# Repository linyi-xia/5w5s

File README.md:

# 5 Watt 5 Seconds (5W5S)
The project was funded by California Energy Commission back in 2011. 
- Phase 1
- Phase 2

# Project Team under project PI Prof. G.P. Li:
- Dr. Jieping Guo: Project lead
- Zac Davis: Phase 1 hardware
- Chris Hurst: Phase 1 hardware
- Linyi Xia: Phase 2 hardware lead engineer, partially firmware and software visualization 
- Liqiang Wang: Phase 2 visualization
- Other members

# Other useful links:
- [ThingSpeak] (https://thingspeak.com/channels/19678)

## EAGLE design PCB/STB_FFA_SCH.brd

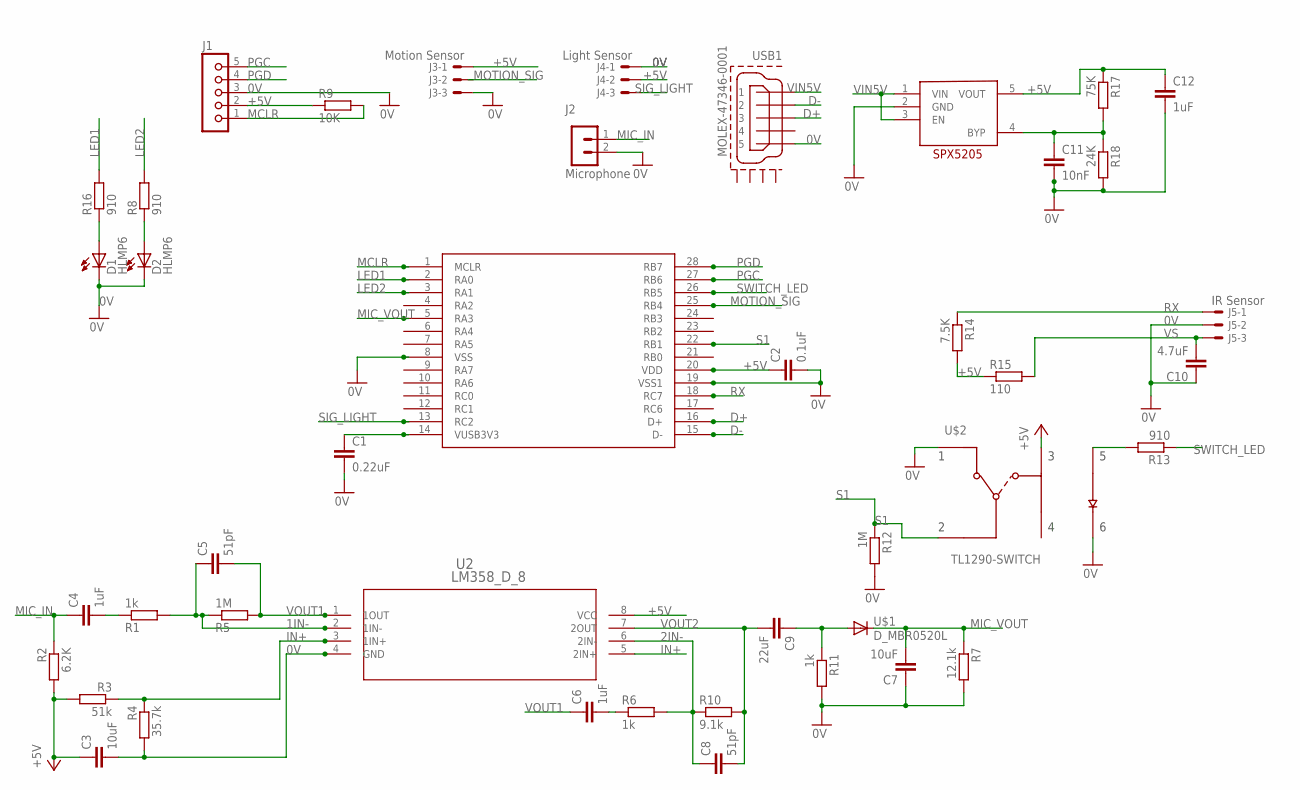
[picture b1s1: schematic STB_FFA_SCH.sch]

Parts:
C1: 0.22uF; C0805
C2: 0.1uF; C0805
C3, C7: 10uF; C0805
C4, C6, C12: 1uF; C0805
C5, C8: 51pF; C0805
C9: 22uF; C0805
C10: 4.7uF; C0805
C11: 10nF; C0805
D1, D2: HLMP6
J1: JU05
J2: Microphone; MA02-1
J3: Motion Sensor; 22-23-2031
J4: Light Sensor; 22-23-2031
J5: IR Sensor; 22-23-2031
R1, R6, R11: 1k; R0805
R2: 6.2K; R0805
R3: 51k; R0805
R4: 35.7k; R0805
R5, R12: 1M; R0805
R7: 12.1k; R0805
R8, R13, R16: 910; R0805
R9: 10K; R0805
R10: 9.1k; R0805
R14: 7.5K; R0805
R15: 110; R0805
R17: 75K; R0805
R18: 24K; R0805
U2: LM358_D_8; D8
U$1: D_MBR0520L
U$2: TL1290-SWITCH
U$3: SPX5205; SOT23-5
U$4: PIC18F25K500; SSOP28
USB1: MOLEX-47346-0001; MOLEX-47364-0001

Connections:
0V: C1.2, C2.2, C3.2, C7.1, C10.1, C11.2, C12.2, D1.K, D2.K, J1.3, J2.2, J3.3, J4.1, J5.2, R4.2, R7.2, R11.2, R12.2, R18.2, U2.4 (GND), U$2.1, U$2.6, U$3.2 (GND), U$4.8 (VSS), U$4.19 (VSS1), USB1.5
1IN-: C5.1, R1.2, R5.1, U2.2 (1IN-)
2IN-: C8.1, R6.2, R10.1, U2.6 (2IN-)
+5V: C2.1, C3.1, C12.1, J1.2, J3.1, J4.2, R2.2, R3.2, R9.1, R14.2, R15.1, R17.1, U2.8 (VCC), U$2.3, U$3.5 (VOUT), U$4.20 (VDD)
D+: U$4.16 (D+), USB1.3
D-: U$4.15 (D-), USB1.2
IN+: R3.1, R4.1, U2.3 (1IN+), U2.5 (2IN+)
LED1: R16.2, U$4.2 (RA0)
LED2: R8.2, U$4.3 (RA1)
MCLR: J1.1, R9.2, U$4.1 (MCLR)
MIC_IN: C4.1, J2.1, R2.1
MIC_VOUT: C7.2, R7.1, U$1.C, U$4.5 (RA3)
MOTION_SIG: U$4.25 (RB4)
unnamed: C1.1, U$4.14 (VUSB3V3)
unnamed: D2.A, R8.1
unnamed: C9.1, R11.1, U$1.A
unnamed: C6.2, R6.1
unnamed: R13.2, U$2.5
unnamed: D1.A, R16.1
unnamed: C4.2, R1.1
unnamed: C11.1, R17.2, R18.1, U$3.4 (BYP)
PGC: J1.5, U$4.27 (RB6)
PGD: J1.4, U$4.28 (RB7)
RX: J5.1, R14.1, U$4.18 (RC7)
S1: R12.1, U$2.2, U$4.22 (RB1)
SIG_LIGHT: J4.3, U$4.13 (RC2)
SWITCH_LED: R13.1, U$4.26 (RB5)
VIN5V: U$3.1 (VIN), U$3.3 (EN), USB1.1
VOUT1: C5.2, C6.1, R5.2, U2.1 (1OUT)
VOUT2: C8.2, C9.2, R10.2, U2.7 (2OUT)
VS: C10.2, J5.3, R15.2

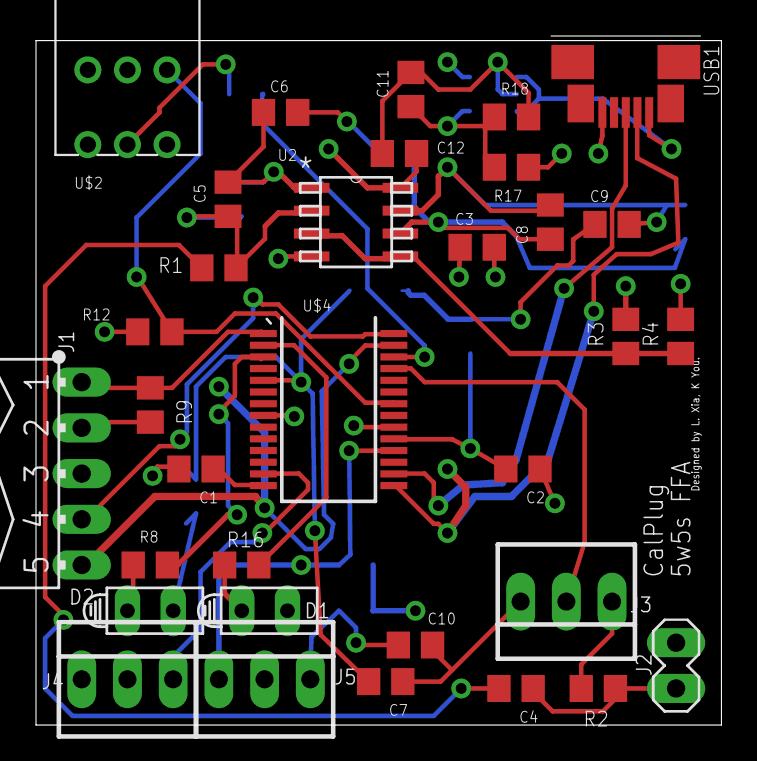
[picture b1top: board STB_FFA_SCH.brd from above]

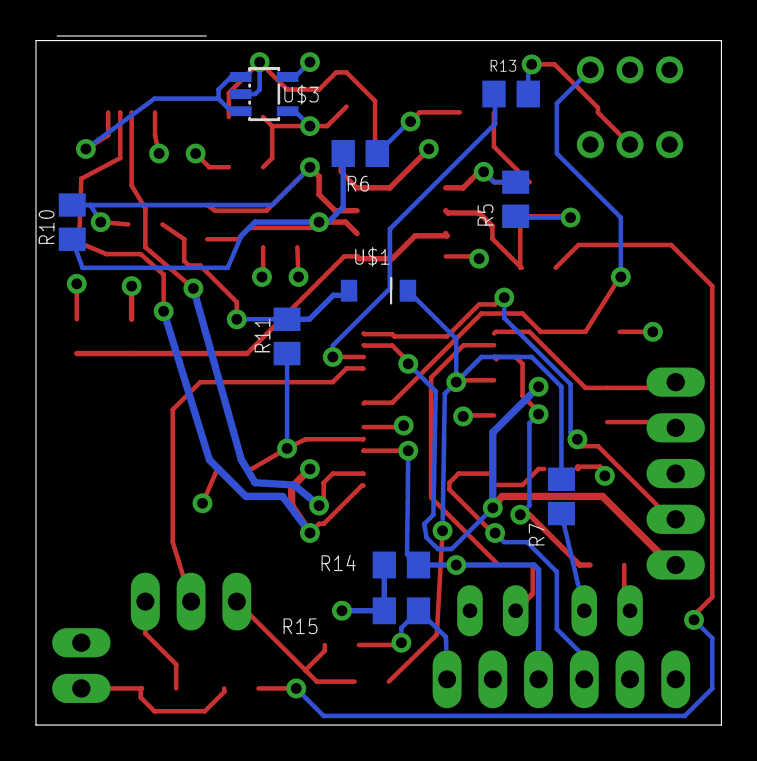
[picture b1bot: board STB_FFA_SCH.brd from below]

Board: 4 copper layers, 38.1 x 38.3 mm, 43 parts (10 on the bottom side), 30 nets.

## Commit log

2016-12-06 Initial
2016-12-06 Initial readme
2016-12-06 ThingSpeak Phase 2 demo
2016-12-06 added ThingSpeak link
2016-12-06 Firmware
2016-12-06 File upload
